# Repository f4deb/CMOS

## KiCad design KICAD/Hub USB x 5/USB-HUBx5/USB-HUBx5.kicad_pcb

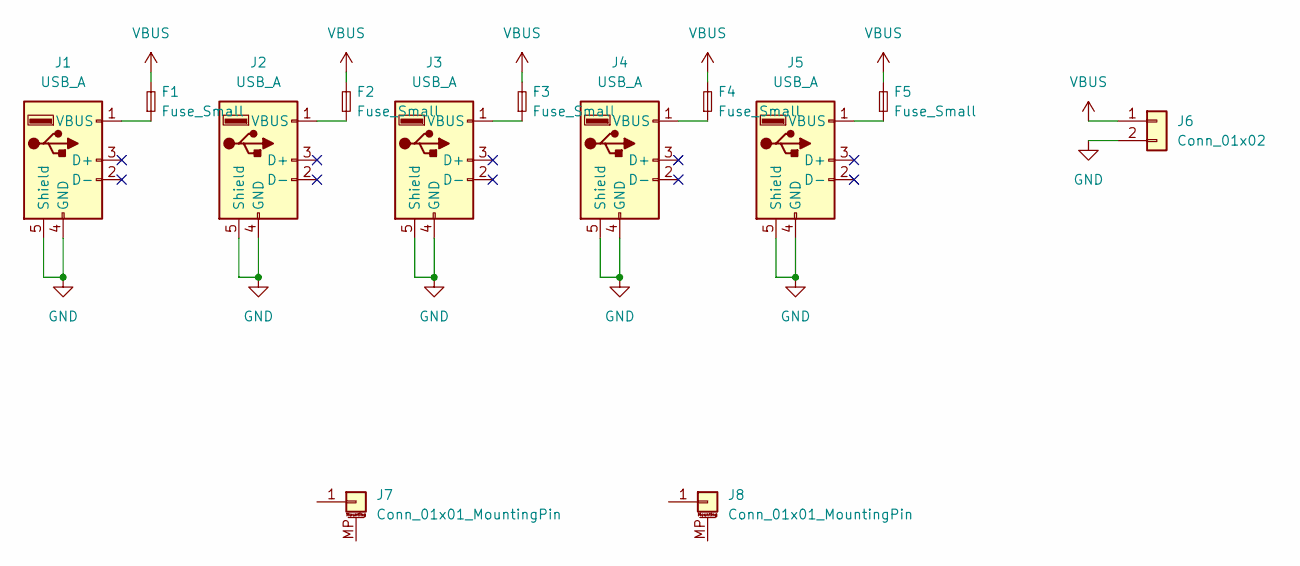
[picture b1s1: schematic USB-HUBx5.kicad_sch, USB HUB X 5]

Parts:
F1, F2, F3, F4, F5: Fuse_Small; Fuseholder_Cylinder-5x20mm_Schurter_0031_8201_Horizontal_Op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
J1, J2, J3, J4, J5: USB_A; USB_A_Wuerth_614004134726_Horizontal
J6: Conn_01x02; PhoenixContact_MSTBA_2,5_2-G-5,08_1x02_P5.08mm_Horizontal
J7, J8: Conn_01x01_MountingPin; Pin_D1.0mm_L10.0mm_LooseFit

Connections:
GND: J1.4 (GND), J1.5 (Shield), J2.4 (GND), J2.5 (Shield), J3.4 (GND), J3.5 (Shield), J4.4 (GND), J4.5 (Shield), J5.4 (GND), J5.5 (Shield), J6.2
unnamed: F1.1, J1.1 (VBUS)
unnamed: F2.1, J2.1 (VBUS)
unnamed: F3.1, J3.1 (VBUS)
unnamed: F4.1, J4.1 (VBUS)
unnamed: F5.1, J5.1 (VBUS)
VBUS: F1.2, F2.2, F3.2, F4.2, F5.2, J6.1

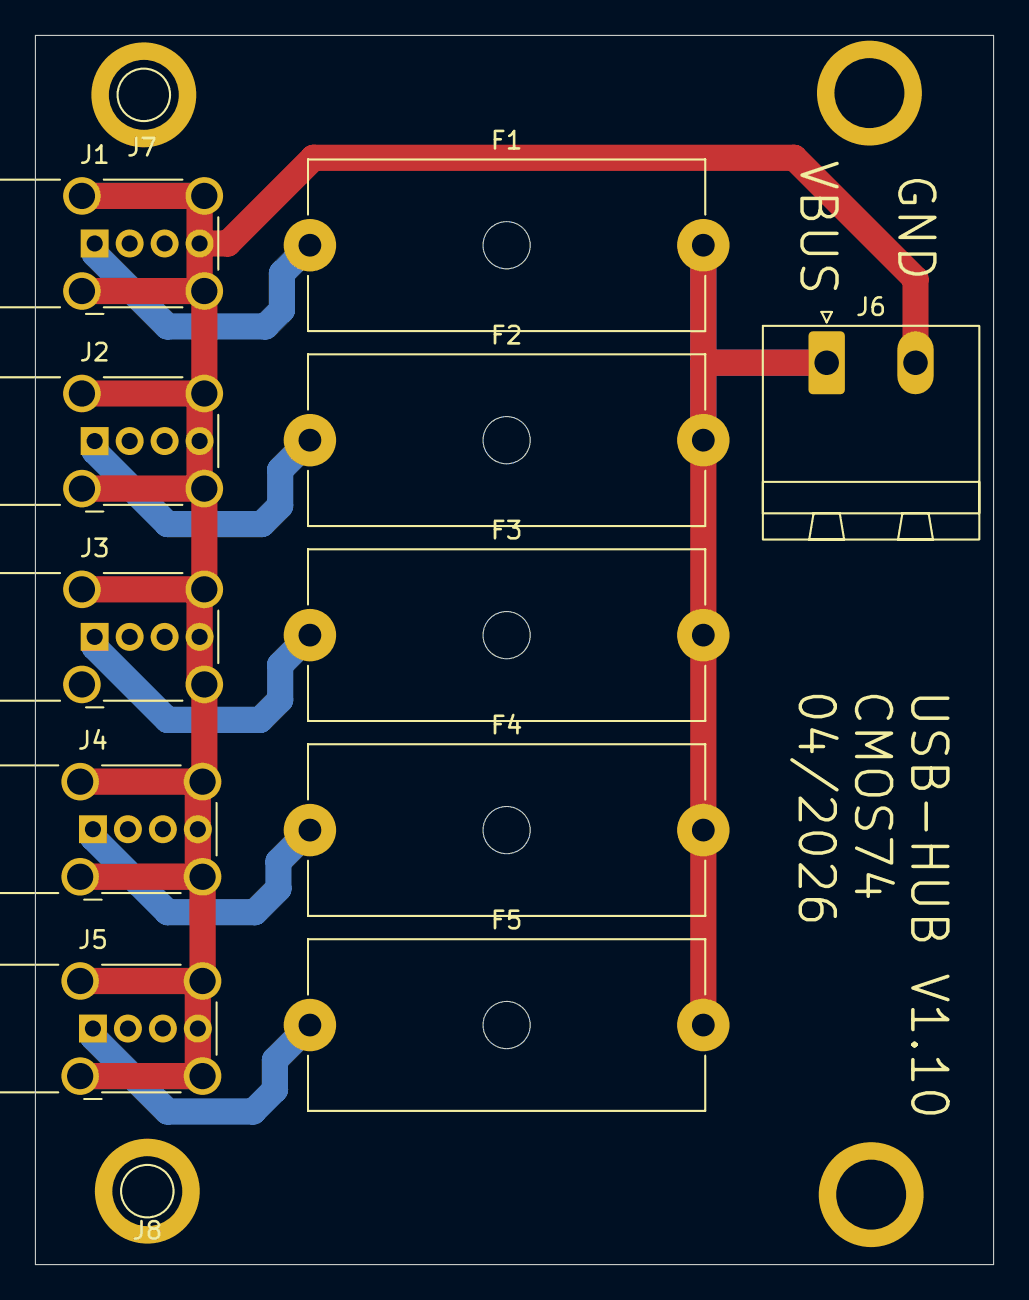
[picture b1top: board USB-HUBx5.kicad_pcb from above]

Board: 2 copper layers, 54.8 x 70.3 mm, 13 parts (0 on the bottom side), 7 nets.

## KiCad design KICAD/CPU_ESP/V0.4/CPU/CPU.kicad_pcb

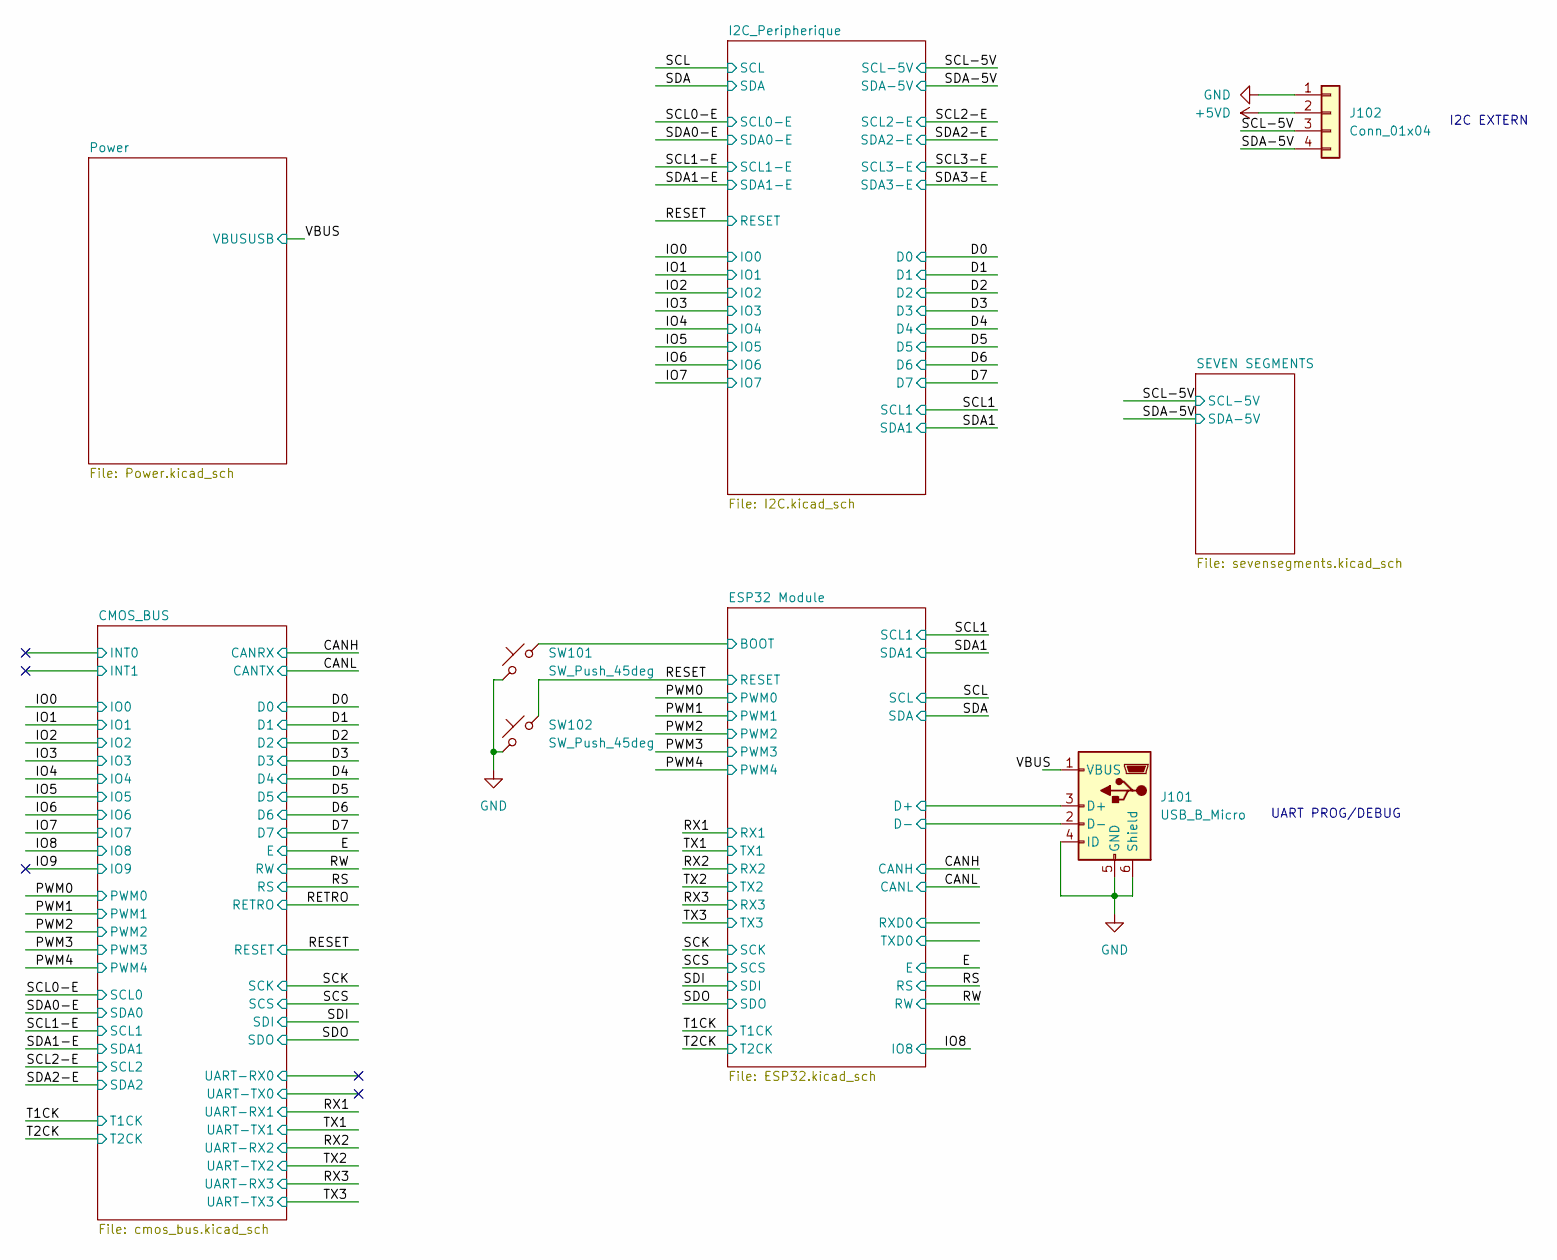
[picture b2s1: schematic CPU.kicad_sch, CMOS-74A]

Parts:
J101: USB_B_Micro; USB_Micro-B_Amphenol_10118194-0001LF_Horizontal
J102: Conn_01x04; JST_GH_SM04B-GHS-TB_1x04-1MP_P1.25mm_Horizontal
SW101: SW_Push_45deg; SW_SPST_CK_RS282G05A3
SW102: SW_Push_45deg; SW_Tactile_SKHH_Angled

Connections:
+5VD: J102.2; also elsewhere on the board
/ESP32 Module/BOOT: SW101.2; also elsewhere on the board
/ESP32 Module/D+: J101.3 (D+); also elsewhere on the board
/ESP32 Module/D-: J101.2 (D-); also elsewhere on the board
/RESET: SW102.2; also elsewhere on the board
/SCL-5V: J102.3; also elsewhere on the board
/SDA-5V: J102.4; also elsewhere on the board
/VBUS: J101.1 (VBUS); also elsewhere on the board
GND: J101.4 (ID), J101.5 (GND), J101.6 (Shield), J102.1, SW101.1, SW102.1; also elsewhere on the board

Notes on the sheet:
UART PROG/DEBUG
I2C EXTERN

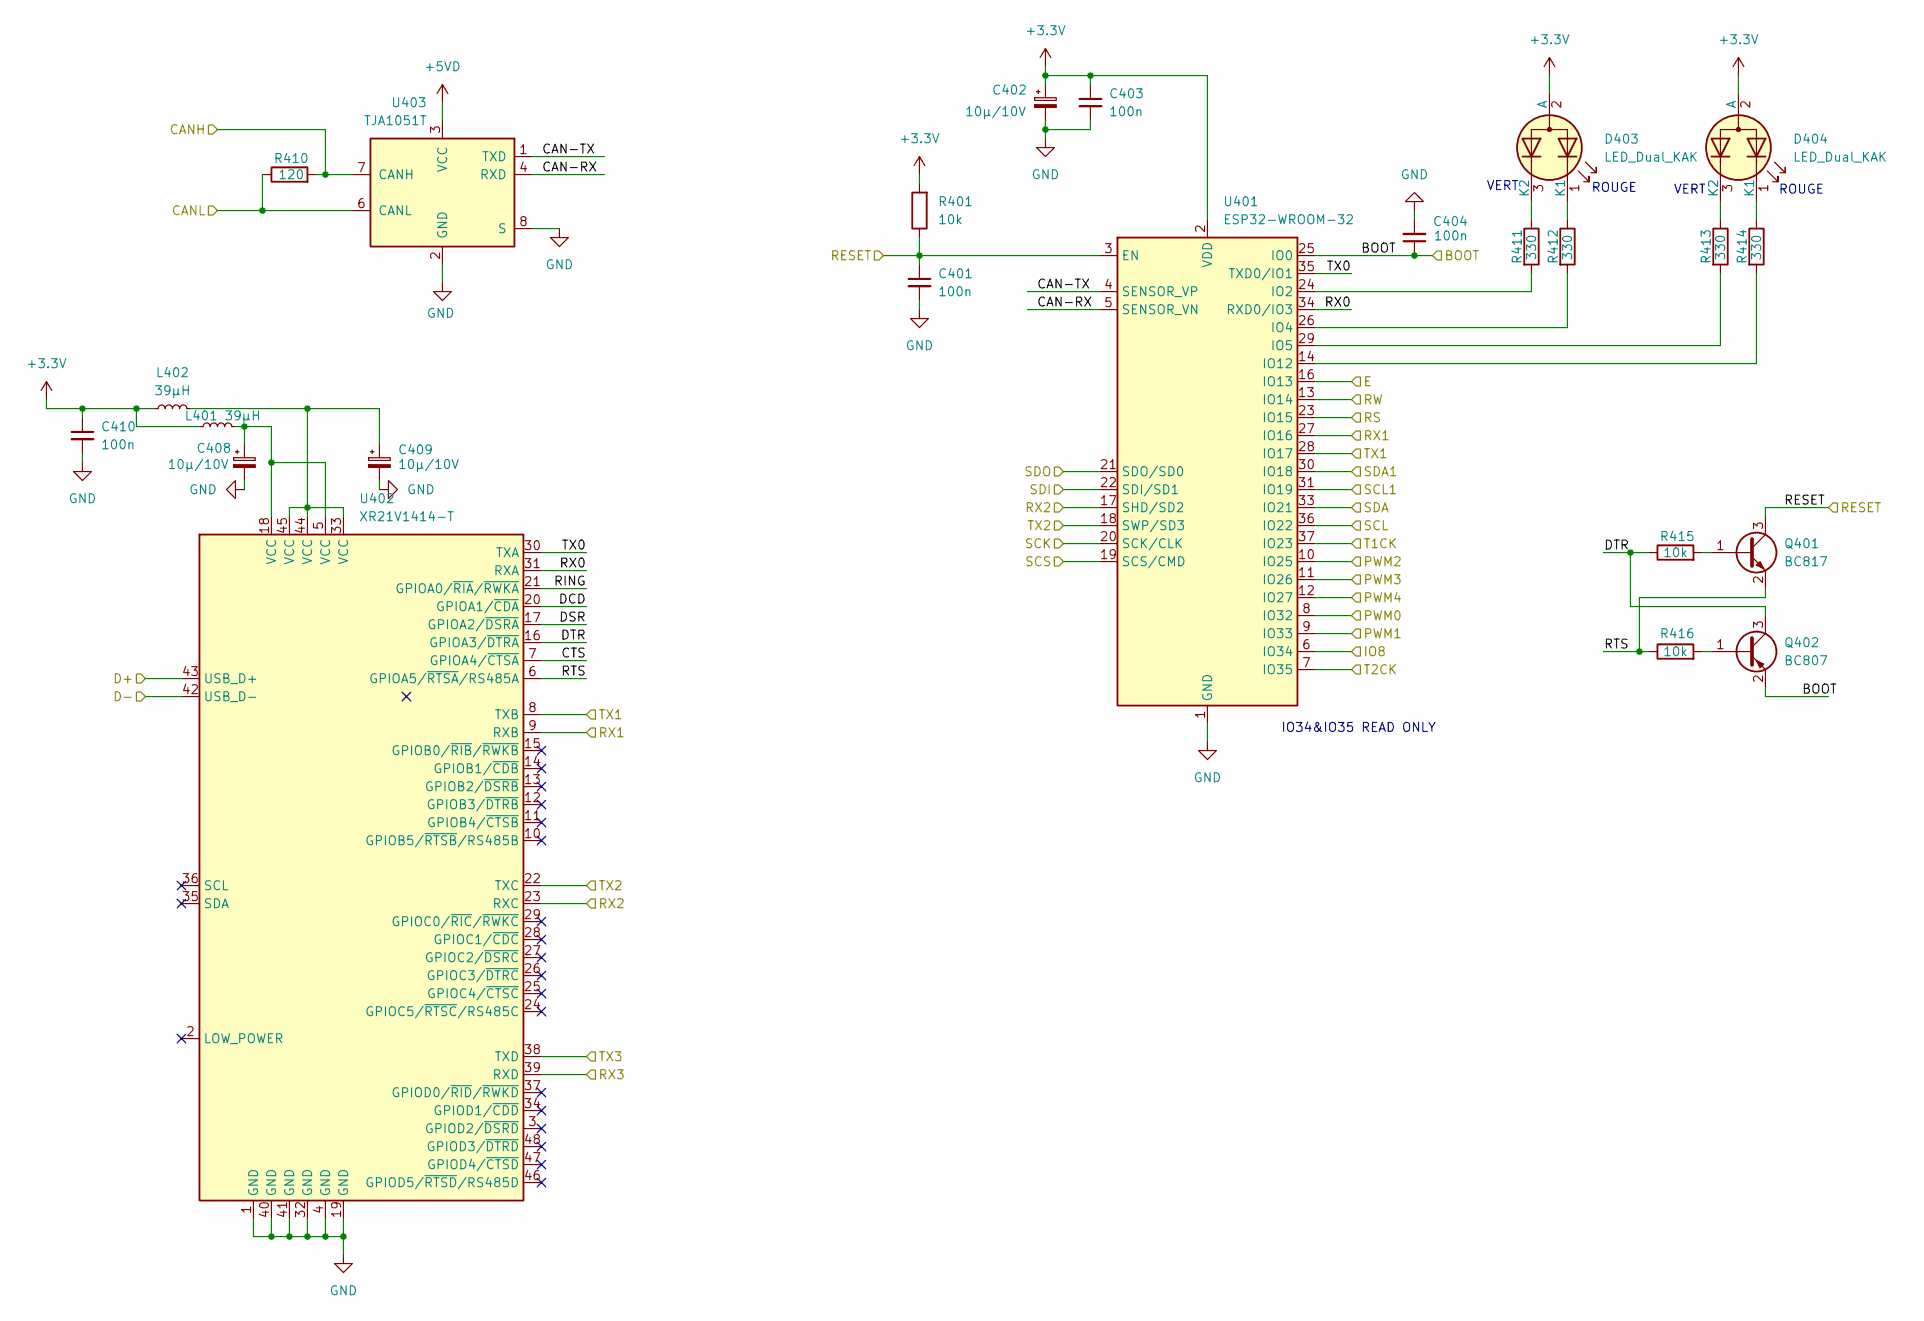
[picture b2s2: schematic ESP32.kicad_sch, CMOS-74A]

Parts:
C401, C403, C404: 100n; C_0603_1608Metric
C402: 10µ/10V; CP_EIA-3216-10_Kemet-I
C408, C409: 10µ/10V; CP_EIA-3216-12_Kemet-S_HandSolder
C410: 100n; C_0603_1608Metric_Pad1.08x0.95mm_HandSolder
D403, D404: LED_Dual_KAK; LED_Kingbright_KPA-3010_3x2x1mm
L401, L402: 39µH; C_2220_5750Metric
Q401: BC817; SOT-23
Q402: BC807; SOT-23
R401, R415, R416: 10k; R_0603_1608Metric
R410: 120; R_1206_3216Metric
R411, R412, R413, R414: 330; R_0603_1608Metric
U401: ESP32-WROOM-32
U402: XR21V1414-T; TQFP-48_7x7mm_P0.5mm
U403: TJA1051T; SOIC-8_3.9x4.9mm_P1.27mm

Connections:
+3.3V: C402.1, C403.1, C410.1, D403.2 (A), D404.2 (A), L401.1, L402.1, R401.2, U401.2 (VDD); also elsewhere on the board
+5VD: U403.3 (VCC); also elsewhere on the board
/CANH: R410.2, U403.7 (CANH); also elsewhere on the board
/CANL: R410.1, U403.6 (CANL); also elsewhere on the board
/E: U401.16 (IO13); also elsewhere on the board
/ESP32 Module/BOOT: C404.1, Q402.2 (E), U401.25 (IO0); also elsewhere on the board
/ESP32 Module/CAN-RX: U401.5 (SENSOR_VN), U403.4 (RXD)
/ESP32 Module/CAN-TX: U401.4 (SENSOR_VP), U403.1 (TXD)
/ESP32 Module/CTS: U402.7 (GPIOA4/~CTSA)
/ESP32 Module/D+: U402.43 (USB_D+); also elsewhere on the board
/ESP32 Module/D-: U402.42 (USB_D-); also elsewhere on the board
/ESP32 Module/DCD: U402.20 (GPIOA1/~CDA)
/ESP32 Module/DSR: U402.17 (GPIOA2/~DSRA)
/ESP32 Module/DTR: Q402.3 (C), R415.1, U402.16 (GPIOA3/~DTRA)
/ESP32 Module/RING: U402.21 (GPIOA0/~RIA/~RWKA)
/ESP32 Module/RTS: Q401.2 (E), R416.1, U402.6 (GPIOA5/~RTSA/RS485A)
/ESP32 Module/RX0: U401.34 (RXD0/IO3), U402.31 (RXA)
/ESP32 Module/TX0: U401.35 (TXD0/IO1), U402.30 (TXA)
/IO8: U401.6 (IO34); also elsewhere on the board
/PWM0: U401.8 (IO32); also elsewhere on the board
/PWM1: U401.9 (IO33); also elsewhere on the board
/PWM2: U401.10 (IO25); also elsewhere on the board
/PWM3: U401.11 (IO26); also elsewhere on the board
/PWM4: U401.12 (IO27); also elsewhere on the board
/RESET: C401.1, Q401.3 (C), R401.1, U401.3 (EN); also elsewhere on the board
/RS: U401.23 (IO15); also elsewhere on the board
/RW: U401.13 (IO14); also elsewhere on the board
/RX1: U401.27 (IO16), U402.9 (RXB); also elsewhere on the board
/RX2: U401.17 (SHD/SD2), U402.23 (RXC); also elsewhere on the board
/RX3: U402.39 (RXD); also elsewhere on the board
/SCK: U401.20 (SCK/CLK); also elsewhere on the board
/SCL: U401.36 (IO22); also elsewhere on the board
/SCL1: U401.31 (IO19); also elsewhere on the board
/SCS: U401.19 (SCS/CMD); also elsewhere on the board
/SDA: U401.33 (IO21); also elsewhere on the board
/SDA1: U401.30 (IO18); also elsewhere on the board
/SDI: U401.22 (SDI/SD1); also elsewhere on the board
/SDO: U401.21 (SDO/SD0); also elsewhere on the board
/T1CK: U401.37 (IO23); also elsewhere on the board
/T2CK: U401.7 (IO35); also elsewhere on the board
/TX1: U401.28 (IO17), U402.8 (TXB); also elsewhere on the board
/TX2: U401.18 (SWP/SD3), U402.22 (TXC); also elsewhere on the board
GND: C401.2, C402.2, C403.2, C404.2, C408.2, C409.2, C410.2, U401.1 (GND), U401.15 (GND), U401.38 (GND), U401.39 (GND), U402.1 (GND), U402.4 (GND), U402.19 (GND), U402.32 (GND), U402.40 (GND), U402.41 (GND), U403.2 (GND), U403.8 (S); also elsewhere on the board
unnamed: C408.1, L401.2, U402.5 (VCC), U402.18 (VCC)
unnamed: D403.1 (K1), R412.1
unnamed: D403.3 (K2), R411.1
unnamed: D404.1 (K1), R414.1
unnamed: D404.3 (K2), R413.1
unnamed: Q401.1 (B), R415.2
unnamed: Q402.1 (B), R416.2
unnamed: R411.2, U401.24 (IO2)
unnamed: R412.2, U401.26 (IO4)
unnamed: R413.2, U401.29 (IO5)
unnamed: R414.2, U401.14 (IO12)

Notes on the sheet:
VERT
ROUGE
IO34&IO35 READ ONLY

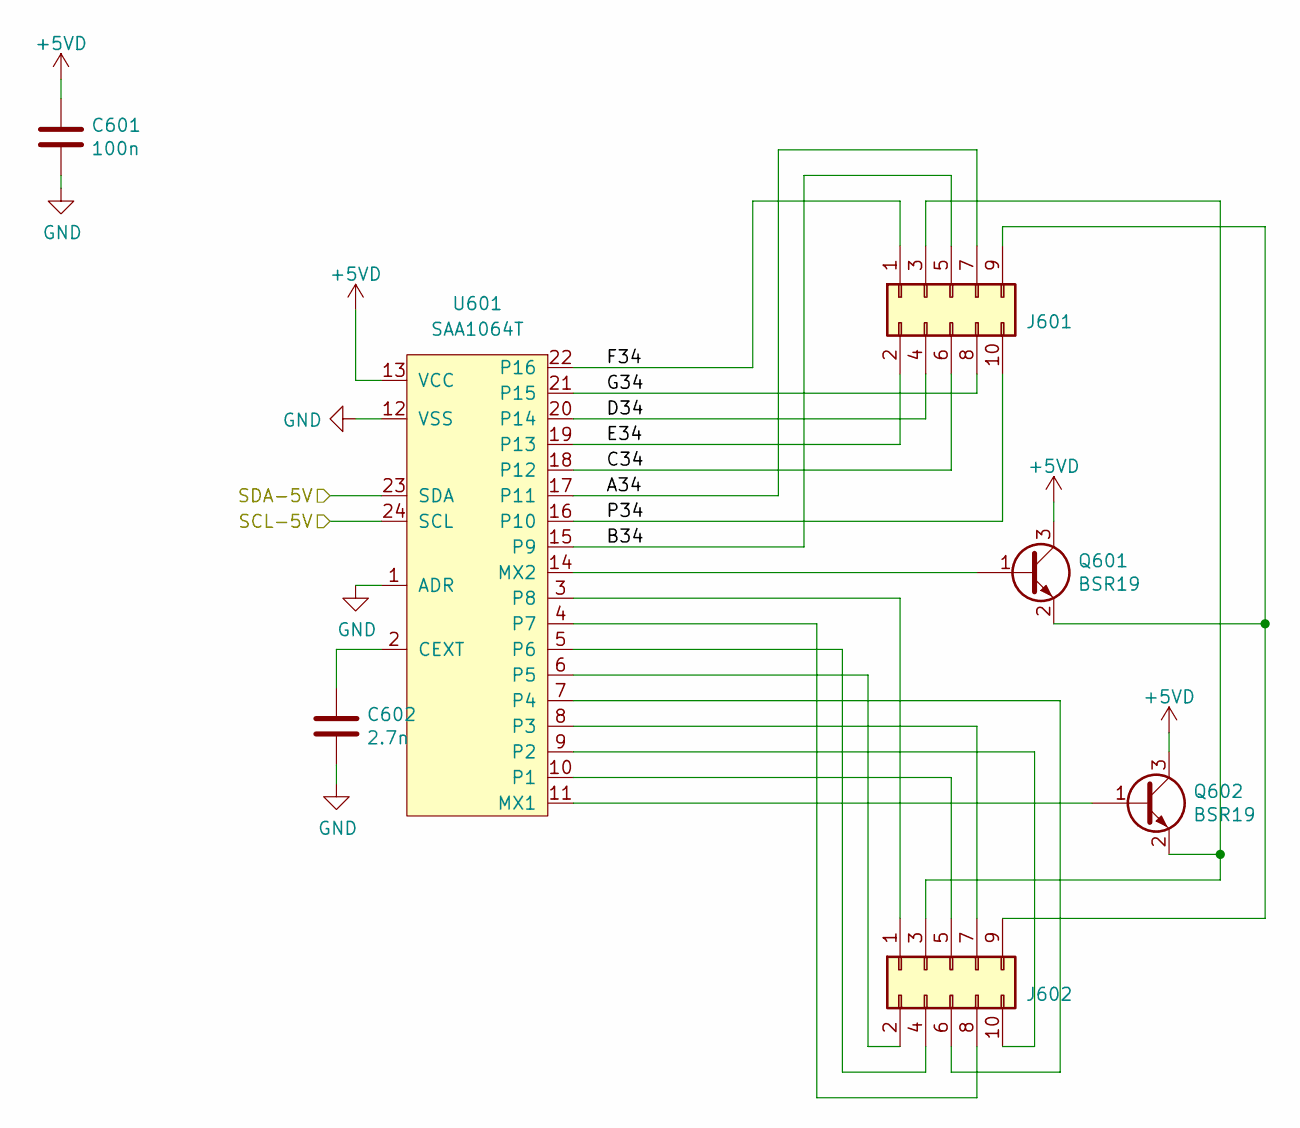
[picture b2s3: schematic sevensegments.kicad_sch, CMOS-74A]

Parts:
C601: 100n; C_0603_1608Metric
C602: 2.7n; C_0603_1608Metric
J601, J602: PinSocket_2x05_P2.54mm_Horizontal
Q601, Q602: BSR19; SOT-23
U601: SAA1064T; SOP-24_7.5x15.4mm_P1.27mm

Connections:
+5VD: C601.1, Q601.3 (C), Q602.3 (C), U601.13 (VCC); also elsewhere on the board
/SCL-5V: U601.24 (SCL); also elsewhere on the board
/SDA-5V: U601.23 (SDA); also elsewhere on the board
/SEVEN SEGMENTS/A34: J601.7, U601.17 (P11)
/SEVEN SEGMENTS/B34: J601.5, U601.15 (P9)
/SEVEN SEGMENTS/C34: J601.6, U601.18 (P12)
/SEVEN SEGMENTS/D34: J601.4, U601.20 (P14)
/SEVEN SEGMENTS/E34: J601.2, U601.19 (P13)
/SEVEN SEGMENTS/F34: J601.1, U601.22 (P16)
/SEVEN SEGMENTS/G34: J601.8, U601.21 (P15)
/SEVEN SEGMENTS/P34: J601.10, U601.16 (P10)
GND: C601.2, C602.2, U601.1 (ADR), U601.12 (VSS); also elsewhere on the board
unnamed: J601.3, J602.3, Q602.2 (E)
unnamed: J601.9, J602.9, Q601.2 (E)
unnamed: J602.1, U601.3 (P8)
unnamed: J602.2, U601.6 (P5)
unnamed: J602.4, U601.5 (P6)
unnamed: J602.5, U601.10 (P1)
unnamed: J602.6, U601.7 (P4)
unnamed: J602.7, U601.8 (P3)
unnamed: J602.8, U601.4 (P7)
unnamed: J602.10, U601.9 (P2)
unnamed: Q601.1 (B), U601.14 (MX2)
unnamed: Q602.1 (B), U601.11 (MX1)
unnamed: C602.1, U601.2 (CEXT)

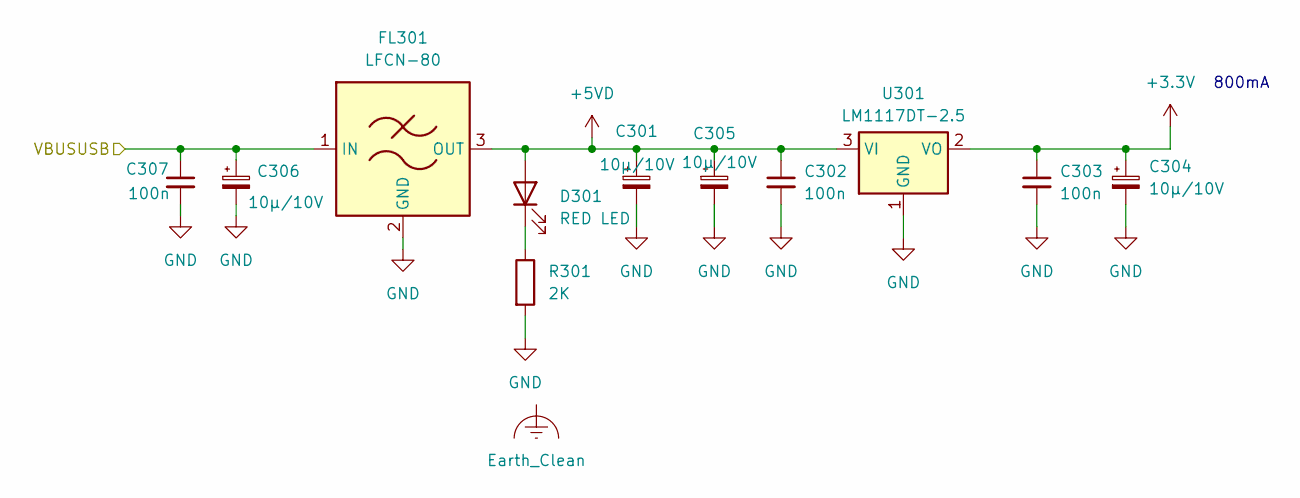
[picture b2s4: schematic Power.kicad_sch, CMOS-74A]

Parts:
C301, C304, C305, C306: 10µ/10V; CP_EIA-3216-12_Kemet-S_HandSolder
C302, C303, C307: 100n; C_0603_1608Metric
D301: RED LED; LED_0603_1608Metric
FL301: LFCN-80; Filter_Mini-Circuits_FV1206
R301: 2K; R_0603_1608Metric
U301: LM1117DT-2.5; TO-252-3_TabPin2

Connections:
+3.3V: C303.1, C304.1, U301.2 (VO); also elsewhere on the board
+5VD: C301.1, C302.1, C305.1, D301.2 (A), FL301.3 (OUT), U301.3 (VI); also elsewhere on the board
/VBUS: C306.1, C307.1, FL301.1 (IN); also elsewhere on the board
GND: C301.2, C302.2, C303.2, C304.2, C305.2, C306.2, C307.2, FL301.2 (GND), FL301.4 (GND), R301.2, U301.1 (GND); also elsewhere on the board
unnamed: D301.1 (K), R301.1

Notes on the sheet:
800mA

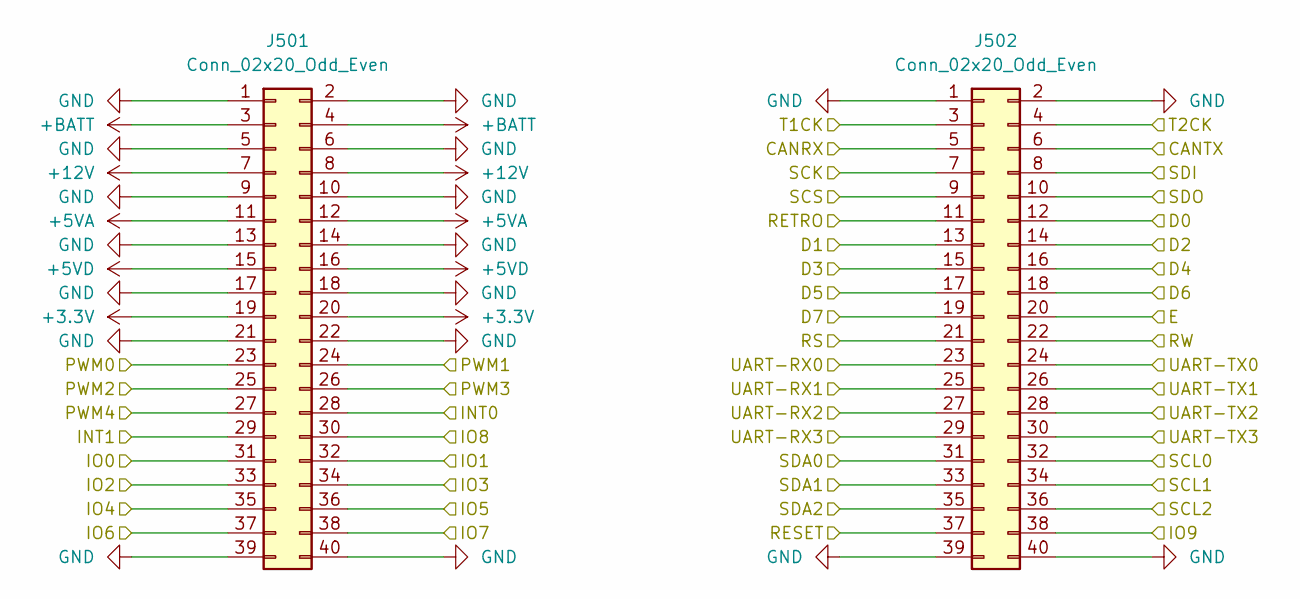
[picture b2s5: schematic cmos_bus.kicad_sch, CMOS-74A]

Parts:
J501, J502: Conn_02x20_Odd_Even; PinSocket_2x20_P2.54mm_Vertical

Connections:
+3.3V: J501.19, J501.20; also elsewhere on the board
+5VA: J501.11, J501.12
+5VD: J501.15, J501.16; also elsewhere on the board
+12V: J501.7, J501.8
+BATT: J501.3, J501.4
/CANH: J502.5; also elsewhere on the board
/CANL: J502.6; also elsewhere on the board
/CMOS_BUS/INT0: J501.28
/CMOS_BUS/INT1: J501.29
/CMOS_BUS/UART-RX0: J502.23
/CMOS_BUS/UART-TX0: J502.24
/D0: J502.12; also elsewhere on the board
/D1: J502.13; also elsewhere on the board
/D2: J502.14; also elsewhere on the board
/D3: J502.15; also elsewhere on the board
/D4: J502.16; also elsewhere on the board
/D5: J502.17; also elsewhere on the board
/D6: J502.18; also elsewhere on the board
/D7: J502.19; also elsewhere on the board
/E: J502.20; also elsewhere on the board
/IO0: J501.31; also elsewhere on the board
/IO1: J501.32; also elsewhere on the board
/IO2: J501.33; also elsewhere on the board
/IO3: J501.34; also elsewhere on the board
/IO4: J501.35; also elsewhere on the board
/IO5: J501.36; also elsewhere on the board
/IO6: J501.37; also elsewhere on the board
/IO7: J501.38; also elsewhere on the board
/IO8: J501.30; also elsewhere on the board
/IO9: J502.38
/PWM0: J501.23; also elsewhere on the board
/PWM1: J501.24; also elsewhere on the board
/PWM2: J501.25; also elsewhere on the board
/PWM3: J501.26; also elsewhere on the board
/PWM4: J501.27; also elsewhere on the board
/RESET: J502.37; also elsewhere on the board
/RETRO: J502.11
/RS: J502.21; also elsewhere on the board
/RW: J502.22; also elsewhere on the board
/RX1: J502.25; also elsewhere on the board
/RX2: J502.27; also elsewhere on the board
/RX3: J502.29; also elsewhere on the board
/SCK: J502.7; also elsewhere on the board
/SCL0-E: J502.32; also elsewhere on the board
/SCL1-E: J502.34; also elsewhere on the board
/SCL2-E: J502.36; also elsewhere on the board
/SCS: J502.9; also elsewhere on the board
/SDA0-E: J502.31; also elsewhere on the board
/SDA1-E: J502.33; also elsewhere on the board
/SDA2-E: J502.35; also elsewhere on the board
/SDI: J502.8; also elsewhere on the board
/SDO: J502.10; also elsewhere on the board
/T1CK: J502.3; also elsewhere on the board
/T2CK: J502.4; also elsewhere on the board
/TX1: J502.26; also elsewhere on the board
/TX2: J502.28; also elsewhere on the board
GND: J501.1, J501.2, J501.5, J501.6, J501.9, J501.10, J501.13, J501.14, J501.17, J501.18, J501.21, J501.22, J501.39, J501.40, J502.1, J502.2, J502.39, J502.40; also elsewhere on the board

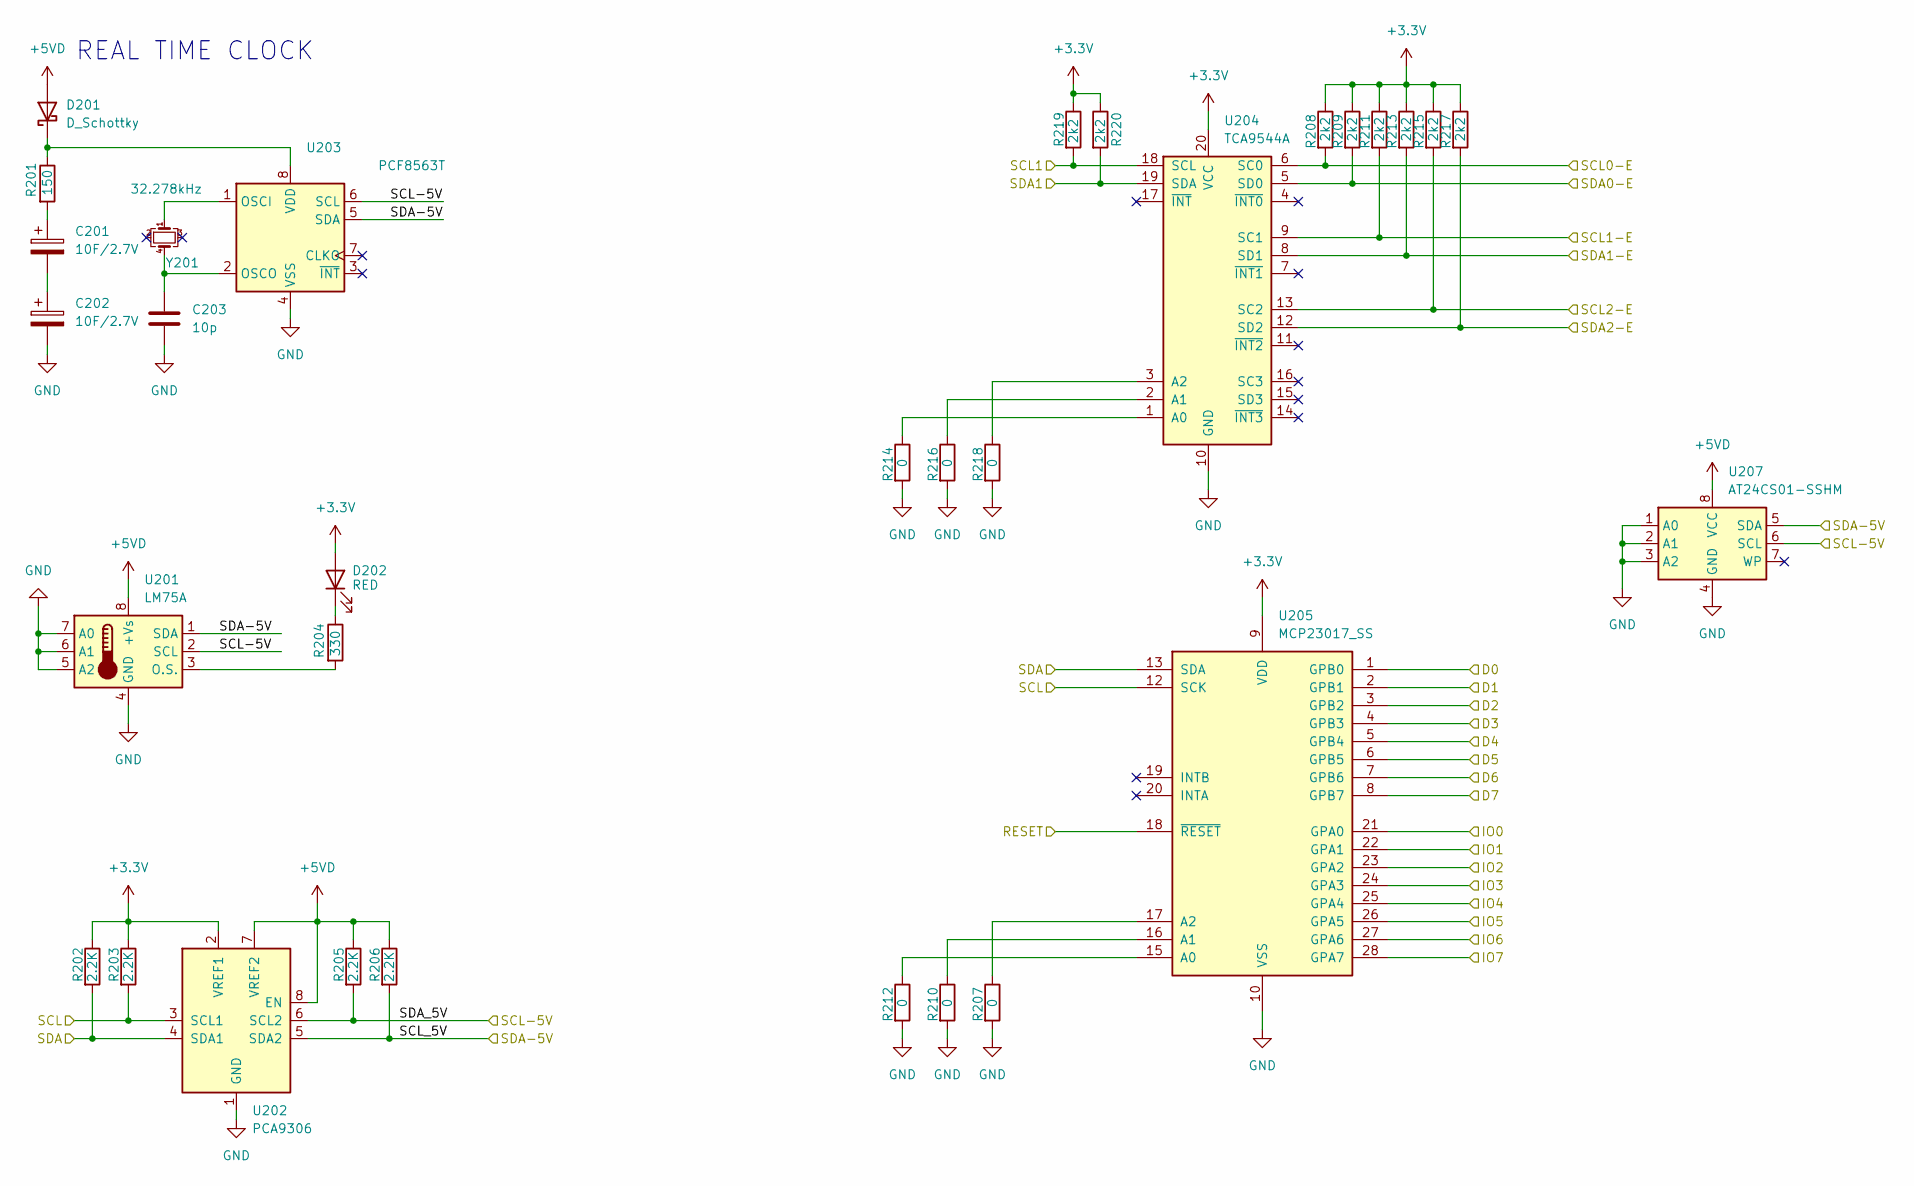
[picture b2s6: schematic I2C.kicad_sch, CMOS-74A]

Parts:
C201, C202: 10F/2.7V; CP_Radial_Tantal_D10.5mm_P5.00mm
C203: 10p; C_0603_1608Metric
D201: D_Schottky; D_2010_5025Metric_Pad1.52x2.65mm_HandSolder
D202: RED; LED_0603_1608Metric
R201: 150; R_0603_1608Metric
R202, R203, R205, R206: 2.2K; R_0603_1608Metric
R204: 330; R_0603_1608Metric
R207, R210, R212, R214, R216, R218: 0; R_0603_1608Metric
R208, R209, R211, R213, R215, R217: 2k2; R_0603_1608Metric_Pad0.98x0.95mm_HandSolder
R219, R220: 2k2; R_0603_1608Metric
U201: LM75A; MSOP-8_3x3mm_P0.65mm
U202: PCA9306; VSSOP-8_2.3x2mm_P0.5mm
U203: PCF8563T; MSOP-8_3x3mm_P0.65mm
U204: TCA9544A; TSSOP-20_4.4x6.5mm_P0.65mm
U205: MCP23017_SS; SSOP-28_5.3x10.2mm_P0.65mm
U207: AT24CS01-SSHM; SOIC-8_5.3x5.3mm_P1.27mm
Y201: 32.278kHz; Crystal_SMD_Abracon_ABS25-4Pin_8.0x3.8mm

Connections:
+3.3V: D202.2 (A), R202.1, R203.1, R208.1, R209.1, R211.1, R213.1, R215.1, R217.1, R219.1, R220.1, U202.2 (VREF1), U204.20 (VCC), U205.9 (VDD); also elsewhere on the board
+5VD: D201.2 (A), R205.1, R206.1, U201.8 (+Vs), U202.7 (VREF2), U202.8 (EN), U207.8 (VCC); also elsewhere on the board
/D0: U205.1 (GPB0); also elsewhere on the board
/D1: U205.2 (GPB1); also elsewhere on the board
/D2: U205.3 (GPB2); also elsewhere on the board
/D3: U205.4 (GPB3); also elsewhere on the board
/D4: U205.5 (GPB4); also elsewhere on the board
/D5: U205.6 (GPB5); also elsewhere on the board
/D6: U205.7 (GPB6); also elsewhere on the board
/D7: U205.8 (GPB7); also elsewhere on the board
/IO0: U205.21 (GPA0); also elsewhere on the board
/IO1: U205.22 (GPA1); also elsewhere on the board
/IO2: U205.23 (GPA2); also elsewhere on the board
/IO3: U205.24 (GPA3); also elsewhere on the board
/IO4: U205.25 (GPA4); also elsewhere on the board
/IO5: U205.26 (GPA5); also elsewhere on the board
/IO6: U205.27 (GPA6); also elsewhere on the board
/IO7: U205.28 (GPA7); also elsewhere on the board
/RESET: U205.18 (~RESET); also elsewhere on the board
/SCL: R203.2, U202.3 (SCL1), U205.12 (SCK); also elsewhere on the board
/SCL0-E: R208.2, U204.6 (SC0); also elsewhere on the board
/SCL1: R219.2, U204.18 (SCL); also elsewhere on the board
/SCL1-E: R211.2, U204.9 (SC1); also elsewhere on the board
/SCL2-E: R215.2, U204.13 (SC2); also elsewhere on the board
/SCL-5V: R205.2, U201.2 (SCL), U202.6 (SCL2), U203.6 (SCL), U207.6 (SCL); also elsewhere on the board
/SDA: R202.2, U202.4 (SDA1), U205.13 (SDA); also elsewhere on the board
/SDA0-E: R209.2, U204.5 (SD0); also elsewhere on the board
/SDA1: R220.2, U204.19 (SDA); also elsewhere on the board
/SDA1-E: R213.2, U204.8 (SD1); also elsewhere on the board
/SDA2-E: R217.2, U204.12 (SD2); also elsewhere on the board
/SDA-5V: R206.2, U201.1 (SDA), U202.5 (SDA2), U203.5 (SDA), U207.5 (SDA); also elsewhere on the board
GND: C202.2, C203.2, R207.2, R210.2, R212.2, R214.2, R216.2, R218.2, U201.4 (GND), U201.5 (A2), U201.6 (A1), U201.7 (A0), U202.1 (GND), U203.4 (VSS), U204.10 (GND), U205.10 (VSS), U207.1 (A0), U207.2 (A1), U207.3 (A2), U207.4 (GND); also elsewhere on the board
unnamed: C201.1, R201.2
unnamed: C201.2, C202.1
unnamed: D201.1 (K), R201.1, U203.8 (VDD)
unnamed: D202.1 (K), R204.1
unnamed: R204.2, U201.3 (O.S.)
unnamed: U203.1 (OSCI), Y201.1
unnamed: C203.1, U203.2 (OSCO), Y201.4
unnamed: R214.1, U204.1 (A0)
unnamed: R216.1, U204.2 (A1)
unnamed: R218.1, U204.3 (A2)
unnamed: R212.1, U205.15 (A0)
unnamed: R210.1, U205.16 (A1)
unnamed: R207.1, U205.17 (A2)

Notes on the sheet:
REAL TIME CLOCK

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
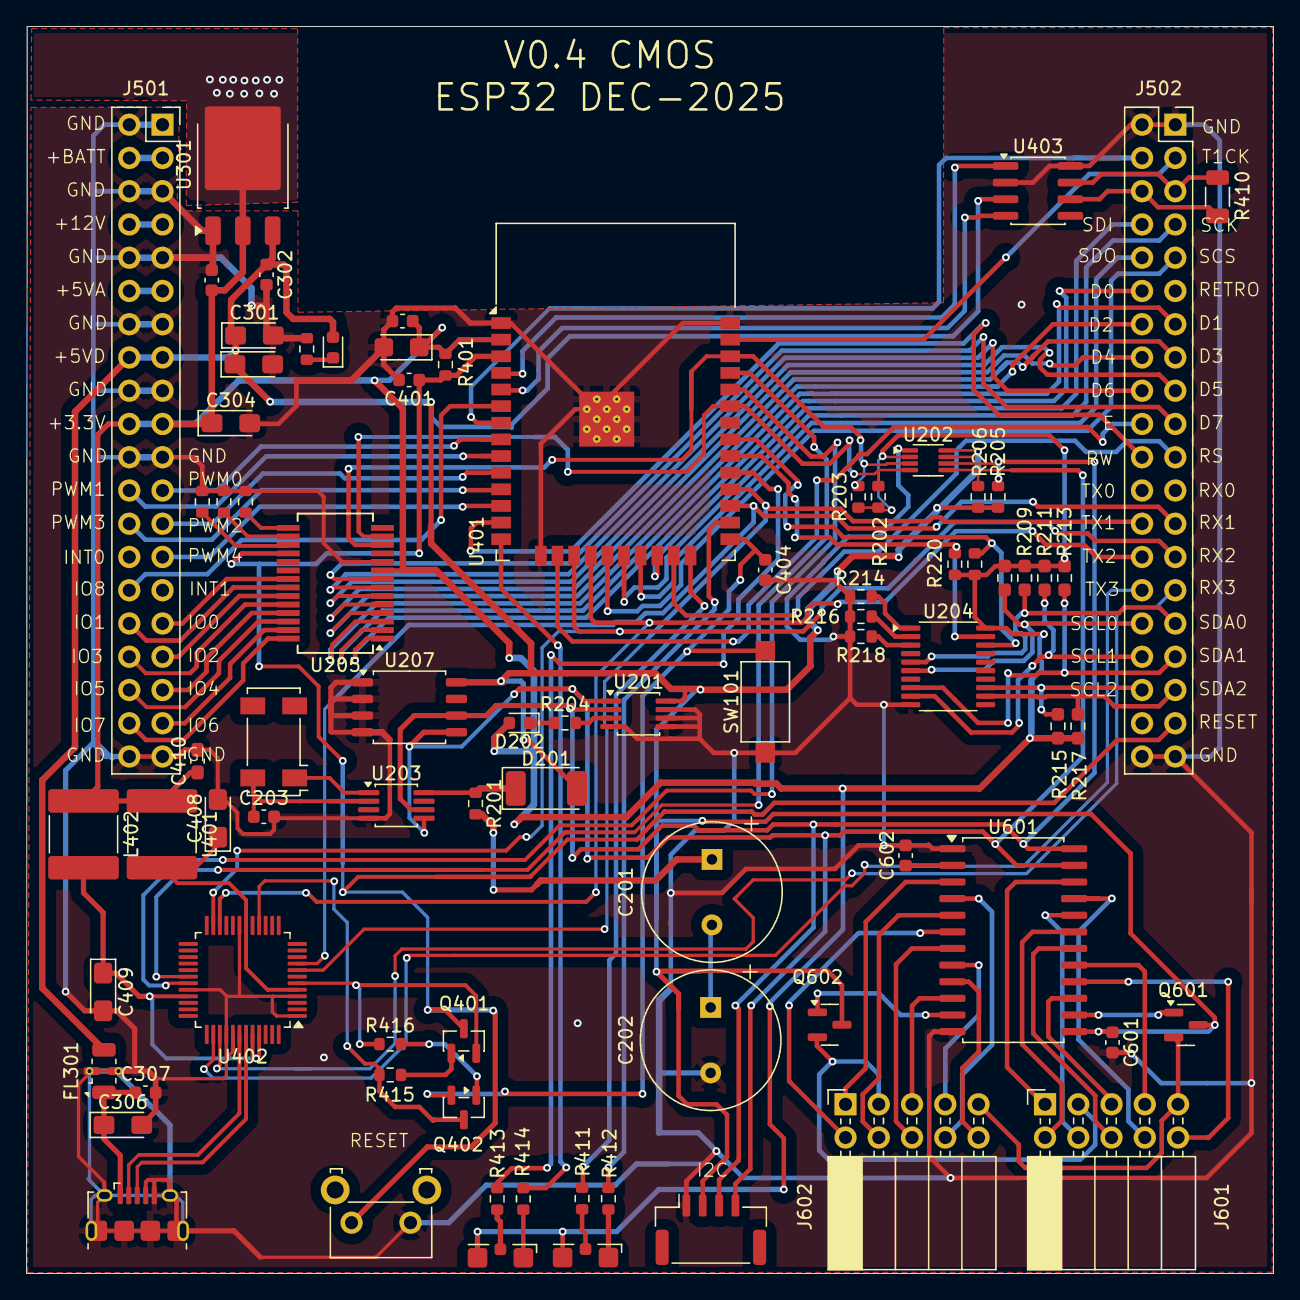
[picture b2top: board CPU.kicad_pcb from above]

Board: 2 copper layers, 95.2 x 95.2 mm, 80 parts (0 on the bottom side), 115 nets.

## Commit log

2025-07-19 Test
2025-07-19 Schematic CPU V0.1
2025-09-26 PCB update
2025-10-05 PCB to control
2025-10-11 VSCODE INIT PROJECT CMOS74-A
2025-10-12 FREECAD Gauche Afficheur
2025-10-15 VSCODE update
2025-10-17 CMakeLists OK
2025-10-22 KICAD CMOS CPU V0.2
2025-10-23 KICADUpdate
2025-10-25 KICAD MAJOR UPDATE V0.2
2025-10-29 VSCODE V0.01
2025-10-30 VSCODE led pointer test
2025-10-30 ledTest Update
2025-11-02 VSCODE Led update
2025-11-02 VSCODE Blink CPU LED OK
2025-11-03 VSCODE Led Pointer begin
2025-11-05 VSCODE Led Ok
2025-11-06 VSCODE Uart
2025-11-11 VSCODE Blink Update
2025-11-11 VSCODE CpuLed Update
2025-11-11 VSCODE blink update
2025-11-12 KICAD 4 UART update
2025-11-16 KICAD 4 UART Update V 0.3
2025-11-19 VSCODE CpuLed Interface Debug
2025-11-20 VSCODE Blink interface Update Bug Ratio SET
2025-11-21 VSCODE CPU LED Command OK
2025-11-21 VSCODE CPU LED Period Interface OK
2025-11-23 VSCODE Led Inteface Update Ok
2025-11-23 VSCODE HELP create
2025-11-25 KICAD XR21V1414 UART V0.4 Update
2025-11-26 KICAD update
2025-12-04 VSCODE TEST
2025-12-13 VSCODE NOK
2025-12-13 VSCODE Help Begin
2025-12-19 save NOK
2026-02-13 MAJ LOGO
2026-02-15 LOGO Ok to print
2026-02-22 MAJ LOGO1
2026-04-27 KICAD HUB USB X 5 V1.1
2026-05-06 VSCODE DESCRIPTOR NOK
2026-05-07 VSCODE DESCRIPTOR NOK ESP LOGE Error
2026-05-08 VSCODE Descriptor OK
2026-05-08 VSCODE UPDATE OK
